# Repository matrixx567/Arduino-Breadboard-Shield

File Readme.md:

# Arduino Breadboard Shield

Eagle Files for a custom shield with a small breadboard.

The [schematic](https://github.com/matrixx567/Arduino-Breadboard-Shield/blob/master/schematic.png) and the [board](https://github.com/matrixx567/Arduino-Breadboard-Shield/blob/master/board.png) design also exists as image files in the repository for a fast and easy view.

## License

This work by Martin Nöhrer is licensed under a [Creative Commons Attribution-ShareAlike 4.0 International License](http://creativecommons.org/licenses/by-sa/4.0/).

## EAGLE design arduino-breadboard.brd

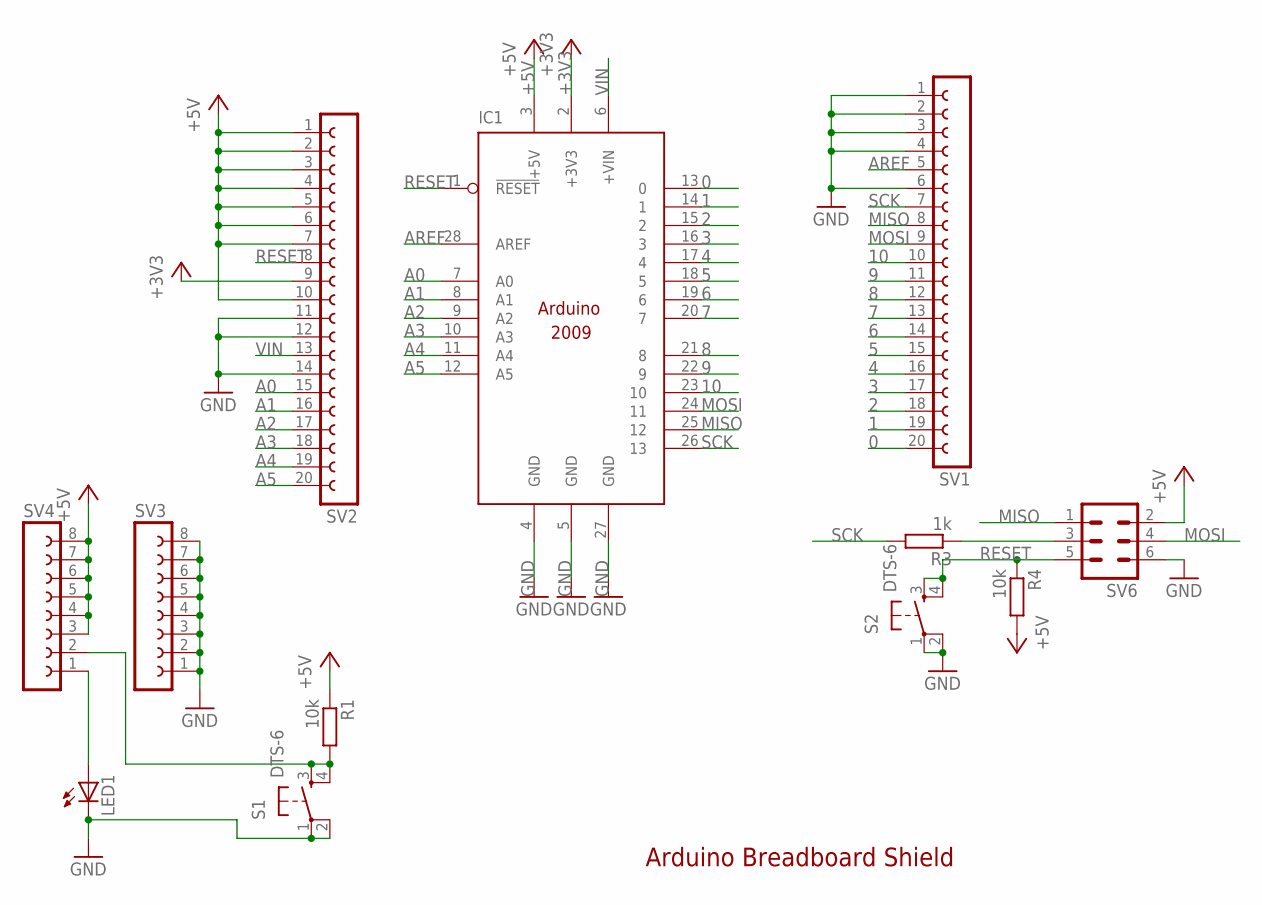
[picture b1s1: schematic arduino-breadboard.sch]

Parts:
IC1: ARDUINO2009_12; ARDUINO2009_2
LED1: LED5MM
R1, R4: 10k; 0207/10
R3: 1k; 0207/10
S1, S2: DTS-6
SV1, SV2: FE20-1; FE20
SV3, SV4: FE08-1; FE08
SV6: MA03-2

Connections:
0: IC1.13 (0), SV1.20
1: IC1.14 (1), SV1.19
2: IC1.15 (2), SV1.18
3: IC1.16 (3), SV1.17
4: IC1.17 (4), SV1.16
5: IC1.18 (5), SV1.15
6: IC1.19 (6), SV1.14
7: IC1.20 (7), SV1.13
8: IC1.21 (8), SV1.12
9: IC1.22 (9), SV1.11
10: IC1.23 (10), SV1.10
+3V3: IC1.2 (+3V3), SV2.9
+5V: IC1.3 (+5V), R1.1, R4.2, SV2.1, SV2.2, SV2.3, SV2.4, SV2.5, SV2.6, SV2.7, SV2.10, SV4.3, SV4.4, SV4.5, SV4.6, SV4.7, SV4.8, SV6.2
A0: IC1.7 (A0), SV2.15
A1: IC1.8 (A1), SV2.16
A2: IC1.9 (A2), SV2.17
A3: IC1.10 (A3), SV2.18
A4: IC1.11 (A4), SV2.19
A5: IC1.12 (A5), SV2.20
AREF: IC1.28 (AREF), SV1.5
GND: IC1.4 (GND), IC1.5 (GND), IC1.27 (GND), LED1.K (C), S1.1, S1.2, S2.1, S2.2, SV1.1, SV1.2, SV1.3, SV1.4, SV1.6, SV2.11, SV2.12, SV2.14, SV3.1, SV3.2, SV3.3, SV3.4, SV3.5, SV3.6, SV3.7, SV3.8, SV6.6
MISO: IC1.25 (12), SV1.8, SV6.1
MOSI: IC1.24 (11), SV1.9, SV6.4
unnamed: LED1.A, SV4.1
unnamed: R3.1, SV6.3
unnamed: R1.2, S1.3, S1.4, SV4.2
RESET: IC1.1 (!RESET), R4.1, S2.3, S2.4, SV2.8, SV6.5
SCK: IC1.26 (13), R3.2, SV1.7
VIN: IC1.6 (+VIN), SV2.13

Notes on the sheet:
Arduino Breadboard Shield

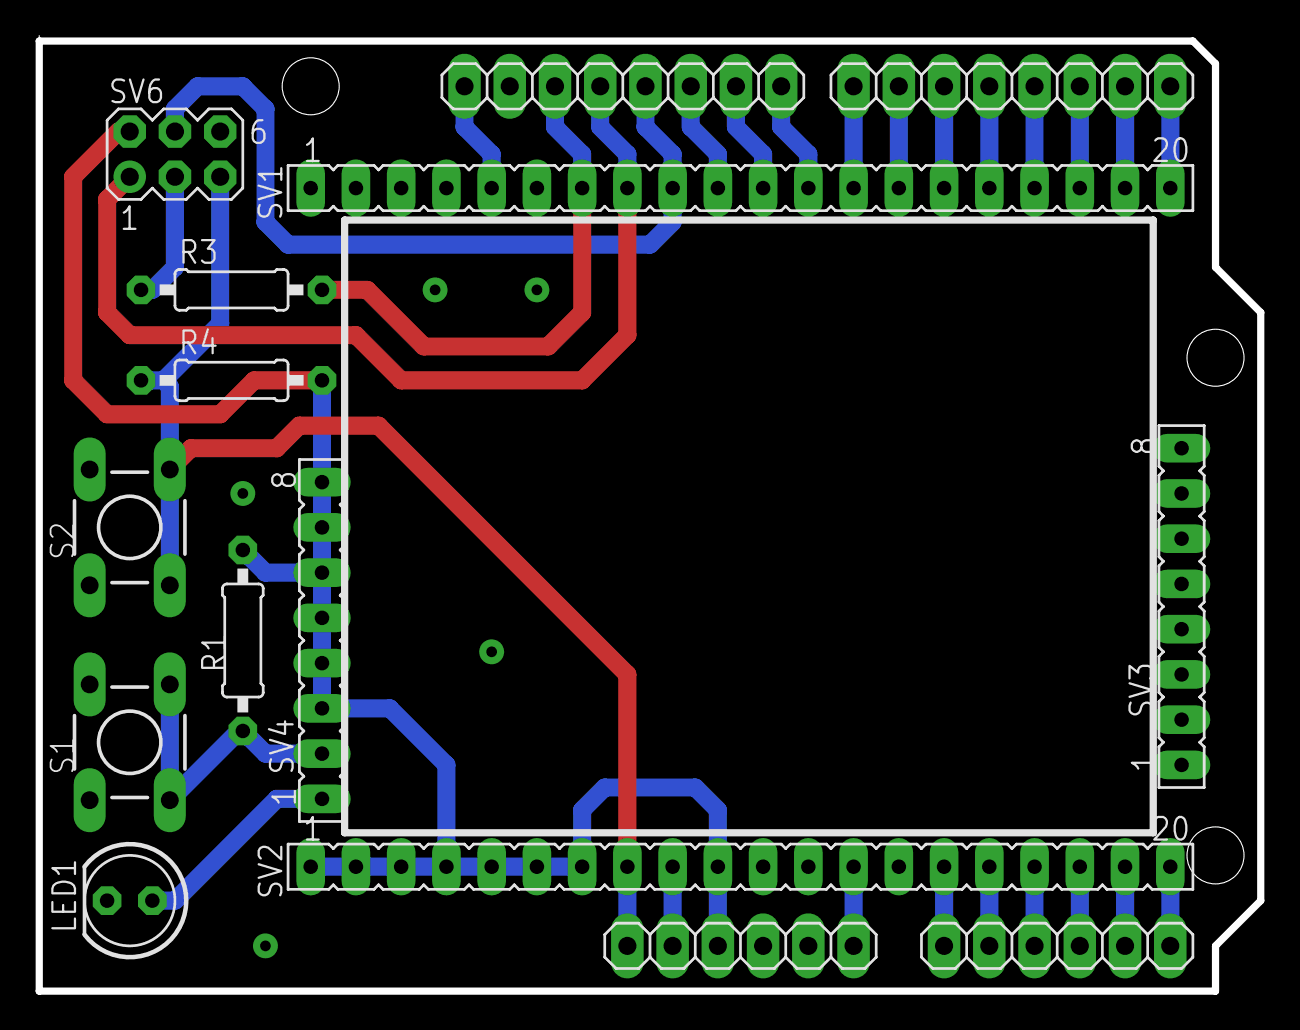
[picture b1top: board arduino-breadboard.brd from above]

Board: 2 copper layers, 68.6 x 53.4 mm, 12 parts (0 on the bottom side), 29 nets.

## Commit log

2015-08-31 Update LICENSE
2015-09-04 Add project image
2015-09-29 correct schematic's frame
